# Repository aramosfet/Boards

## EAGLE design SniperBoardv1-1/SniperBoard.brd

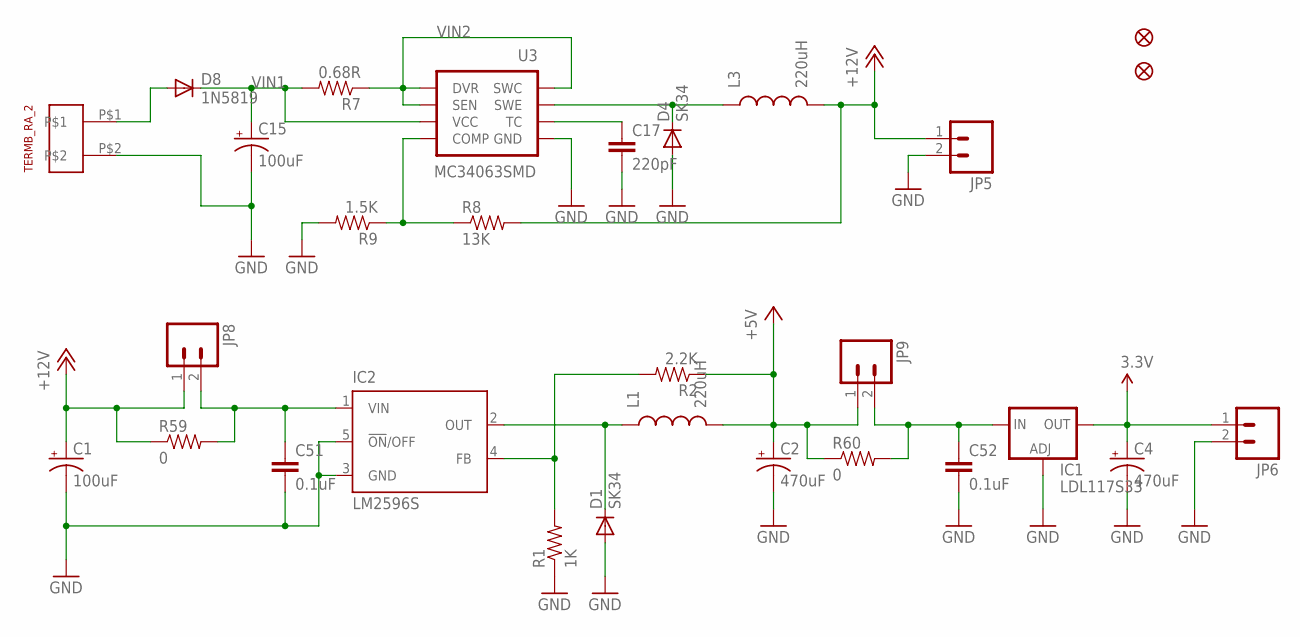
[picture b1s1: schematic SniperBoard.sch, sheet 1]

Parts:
C1, C15: 100uF; PANASONIC_E
C2, C4: 470uF; PANASONIC_E
C17: 220pF; 0805
C51, C52: 0.1uF; 0805
D1, D4: SK34; SMA-DIODE
D8: 1N5819; SMB-DIODE
FID1, FID2: FIDUCIAL1.5X3; FIDUCIAL-1.5X3
IC1: LDL117S33; DPACK
IC2: LM2596S; TO263-5
JP5, JP6: M02POLAR; MOLEX-1X2
JP8, JP9: M02PTH; 1X02
L1, L3: 220uH; RLB914-IND
R1: 1K; 0805
R2: 2.2K; 0805
R7: 0.68R; 0805
R8: 13K; 0805
R9: 1.5K; 0805
R59, R60: 0; 0805
U3: MC34063SMD; SO08
U$2: 1X02_TERMB_RA

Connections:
3.3V: C4.+, IC1.4 (OUT), JP6.1; also elsewhere on the board
+5V: C2.+, JP9.1, L1.P$2 (2), R2.1, R60.1
+12V: C1.+, JP5.1, JP8.1, L3.P$2 (2), R8.2, R59.1; also elsewhere on the board
GND: C1.-, C2.-, C4.-, C15.-, C17.2, C51.2, C52.2, D1.A, D4.A, IC1.1 (ADJ), IC2.3 (GND), IC2.5 (!ON!/OFF), JP5.2, JP6.2, R1.1, R9.2, U3.4 (GND), U$2.P$2; also elsewhere on the board
unnamed: IC2.4 (FB), R1.2, R2.2
unnamed: D1.C, IC2.2 (OUT), L1.P$1 (1)
unnamed: C17.1, U3.3 (TC)
unnamed: D4.C, L3.P$1 (1), U3.2 (SWE)
unnamed: R8.1, R9.1, U3.5 (COMP)
unnamed: D8.A, U$2.P$1
unnamed: C52.1, IC1.3 (IN), JP9.2, R60.2
unnamed: C51.1, IC2.1 (VIN), JP8.2, R59.2
VIN1: C15.+, D8.C, R7.2, U3.6 (VCC)
VIN2: R7.1, U3.1 (SWC), U3.7 (SEN), U3.8 (DVR)

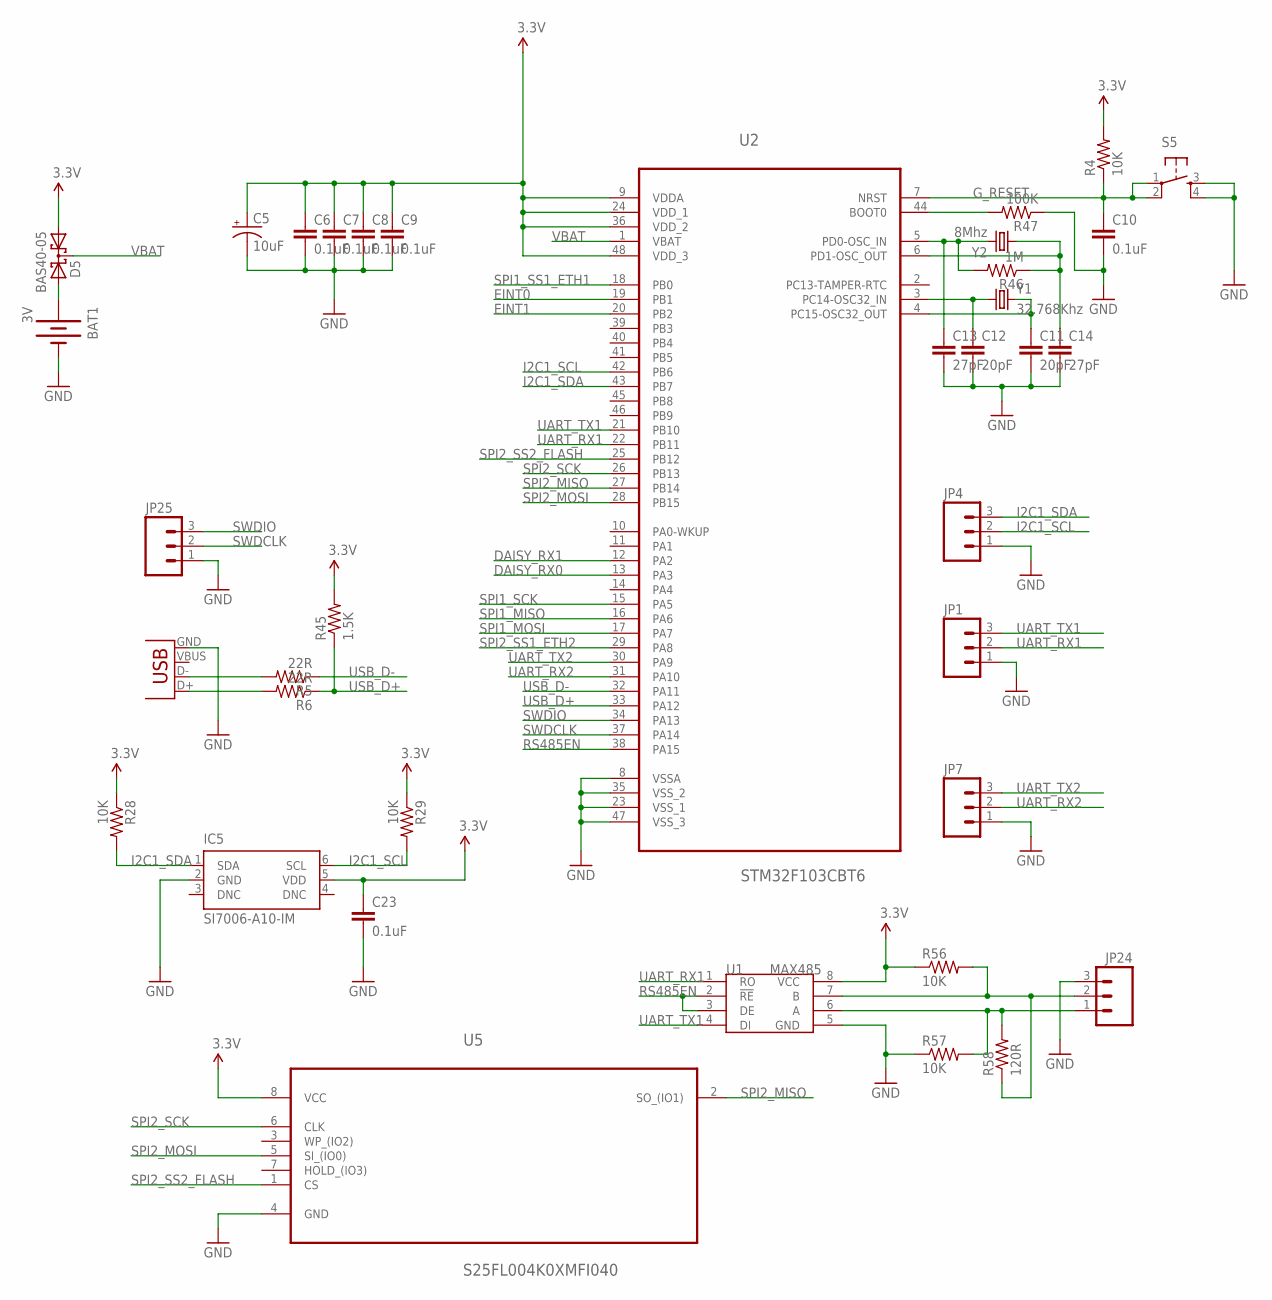
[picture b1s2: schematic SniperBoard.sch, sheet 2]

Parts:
BAT1: 3V; BATTCOM_20MM_PTH
C5: 10uF; EIA3216
C6, C7, C8, C9, C10, C23: 0.1uF; 0805
C11, C12: 20pF; 0805
C13, C14: 27pF; 0805
D5: BAS40-05; SOT23
IC5: SI7006-A10-IM; DFN6-3X3
JP1, JP4, JP7: M03PTH; 1X03
JP3: USB-B; USB-B-PTH
JP24: M03-SCREW-5MM; SCREWTERMINAL-5MM-3
JP25: M03POLAR; MOLEX-1X3
R4, R28, R29, R56, R57: 10K; 0805
R5, R6: 22R; 0805
R45: 1.5K; 0805
R46: 1M; 0805
R47: 100K; 0805
R58: 120R; 1206
S5: TAC_SWITCHPTH; TACTILE-PTH
U1: MAX485; SOP8
U2: STM32F103CBT6; QFP50P900X900X160-48N
U5: S25FL004K0XMFI040; SOIC127P600X175-8N
Y1: 32.768Khz; MC-306
Y2: 8Mhz; HC49US

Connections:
3.3V: C5.A (+), C6.1, C7.1, C8.1, C9.1, C23.1, D5.1 (A1), IC5.5 (VDD), R4.2, R28.1, R29.1, R45.2, R56.1, U1.8 (VCC), U2.9 (VDDA), U2.24 (VDD_1), U2.36 (VDD_2), U2.48 (VDD_3), U5.8 (VCC); also elsewhere on the board
BOOT0: R47.2, U2.44 (BOOT0)
DAISY_RX0: U2.13 (PA3); also elsewhere on the board
DAISY_RX1: U2.12 (PA2); also elsewhere on the board
EINT0: U2.19 (PB1); also elsewhere on the board
EINT1: U2.20 (PB2); also elsewhere on the board
GND: BAT1.2 (-), C5.C (-), C6.2, C7.2, C8.2, C9.2, C10.2, C11.2, C12.2, C13.2, C14.2, C23.2, IC5.2 (GND), JP1.1, JP3.GND, JP4.1, JP7.1, JP24.3, JP25.1, R47.1, R57.1, S5.3, S5.4, U1.5 (GND), U2.8 (VSSA), U2.23 (VSS_1), U2.35 (VSS_2), U2.47 (VSS_3), U5.4 (GND); also elsewhere on the board
G_RESET: C10.1, R4.1, S5.1, S5.2, U2.7 (NRST); also elsewhere on the board
I2C1_SCL: IC5.6 (SCL), JP4.2, R29.2, U2.42 (PB6)
I2C1_SDA: IC5.1 (SDA), JP4.3, R28.2, U2.43 (PB7)
unnamed: BAT1.1 (+), D5.2 (A2)
unnamed: JP24.1, R57.2, R58.2, U1.6 (A)
unnamed: C14.1, R46.1, U2.6 (PD1-OSC_OUT), Y2.1
unnamed: JP3.D-, R5.2
unnamed: JP3.D+, R6.2
unnamed: C12.1, U2.3 (PC14-OSC32_IN), Y1.1
unnamed: C11.1, U2.4 (PC15-OSC32_OUT), Y1.4 (2)
unnamed: C13.1, R46.2, U2.5 (PD0-OSC_IN), Y2.2
unnamed: JP24.2, R56.2, R58.1, U1.7 (B)
RS485EN: U1.2 (!RE), U1.3 (DE), U2.38 (PA15)
SPI1_MISO: U2.16 (PA6); also elsewhere on the board
SPI1_MOSI: U2.17 (PA7); also elsewhere on the board
SPI1_SCK: U2.15 (PA5); also elsewhere on the board
SPI1_SS1_ETH1: U2.18 (PB0); also elsewhere on the board
SPI2_MISO: U2.27 (PB14), U5.2 (SO_(IO1)); also elsewhere on the board
SPI2_MOSI: U2.28 (PB15), U5.5 (SI_(IO0)); also elsewhere on the board
SPI2_SCK: U2.26 (PB13), U5.6 (CLK); also elsewhere on the board
SPI2_SS1_ETH2: U2.29 (PA8); also elsewhere on the board
SPI2_SS2_FLASH: U2.25 (PB12), U5.1 (CS)
SWDCLK: JP25.2, U2.37 (PA14)
SWDIO: JP25.3, U2.34 (PA13)
UART_RX1: JP1.2, U1.1 (RO), U2.22 (PB11)
UART_RX2: JP7.2, U2.31 (PA10); also elsewhere on the board
UART_TX1: JP1.3, U1.4 (DI), U2.21 (PB10)
UART_TX2: JP7.3, U2.30 (PA9); also elsewhere on the board
USB_D+: R6.1, R45.1, U2.33 (PA12)
USB_D-: R5.1, U2.32 (PA11)
VBAT: D5.3 (C), U2.1 (VBAT)

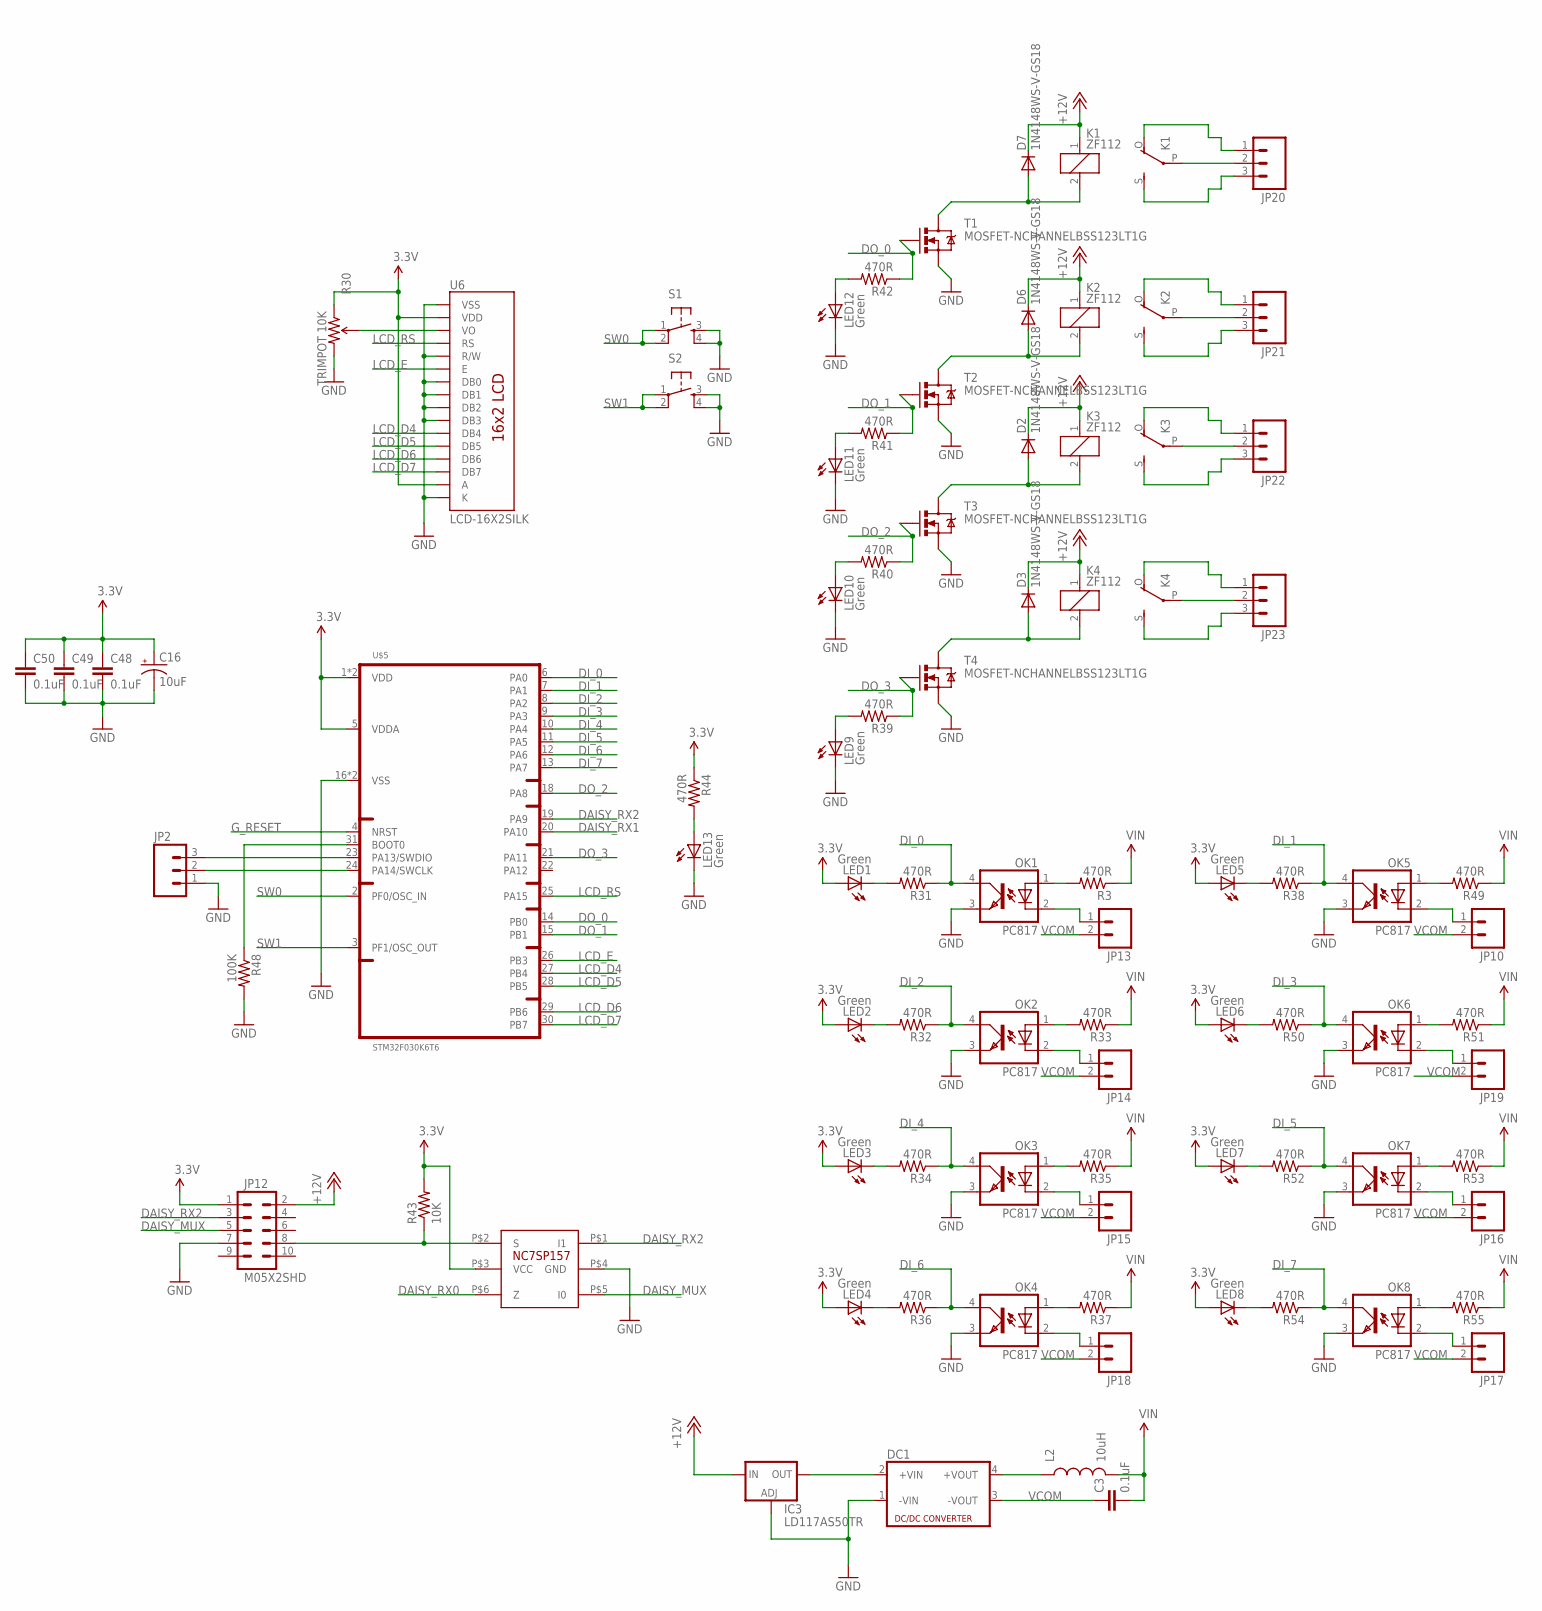
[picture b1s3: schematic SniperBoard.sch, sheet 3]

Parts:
C3, C48, C49, C50: 0.1uF; 0805
C16: 10uF; EIA3216
D2, D3, D6, D7: 1N4148WS-V-GS18; SMA-DIODE_ALT
DC1: NME
IC3: LD117AS50TR; SOT223
JP2: M03POLAR; MOLEX-1X3
JP10, JP13, JP14, JP15, JP16, JP17, JP18, JP19: M025MM; SCREWTERMINAL-5MM-2
JP12: M05X2SHD; 2X5-SHROUDED
JP20, JP21, JP22, JP23: M03-SCREW-5MM; SCREWTERMINAL-5MM-3
K1, K2, K3, K4: ZF112
L2: 10uH; 0805
LED1, LED2, LED3, LED4, LED5, LED6, LED7, LED8, LED9, LED10, LED11, LED12, LED13: Green; LED-1206
OK1, OK2, OK3, OK4, OK5, OK6, OK7, OK8: PC817; DIL04
R3, R31, R32, R33, R34, R35, R36, R37, R38, R39, R40, R41, R42, R44, R49, R50, R51, R52, R53, R54, R55: 470R; 0805
R30: TRIMPOT 10K; TRIM_POT_PTH
R43: 10K; 0805
R48: 100K; 0805
S1, S2: TAC_SWITCHPTH; TACTILE-PTH
T1, T2, T3, T4: MOSFET-NCHANNELBSS123LT1G; SOT23
U6: LCD-16X2SILK; LCD-16X2
U$4: NC7SP157; SC70-6
U$5: STM32F030K6T6; LQFP32-7X7

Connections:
3.3V: C16.A (+), C48.1, C49.1, C50.1, JP12.1, LED1.A, LED2.A, LED3.A, LED4.A, LED5.A, LED6.A, LED7.A, LED8.A, R30.1 (CCW), R43.2, R44.1, U6.2 (VDD), U6.15 (A), U$4.P$3 (VCC), U$5.1 (VDD), U$5.5 (VDDA), U$5.17 (VDD); also elsewhere on the board
+12V: D2.C, D3.C, D6.C, D7.C, IC3.3 (IN), JP12.2, K1.1, K2.1, K3.1, K4.1; also elsewhere on the board
DAISY_MUX: JP12.5, U$4.P$5 (I0)
DAISY_RX0: U$4.P$6 (Z); also elsewhere on the board
DAISY_RX1: U$5.20 (PA10); also elsewhere on the board
DAISY_RX2: JP12.3, U$4.P$1 (I1), U$5.19 (PA9)
DI_0: OK1.4 (COL), R31.1, U$5.6 (PA0)
DI_1: OK5.4 (COL), R38.1, U$5.7 (PA1)
DI_2: OK2.4 (COL), R32.1, U$5.8 (PA2)
DI_3: OK6.4 (COL), R50.1, U$5.9 (PA3)
DI_4: OK3.4 (COL), R34.1, U$5.10 (PA4)
DI_5: OK7.4 (COL), R52.1, U$5.11 (PA5)
DI_6: OK4.4 (COL), R36.1, U$5.12 (PA6)
DI_7: OK8.4 (COL), R54.1, U$5.13 (PA7)
DO_0: R42.1, T1.1 (G), U$5.14 (PB0)
DO_1: R41.1, T2.1 (G), U$5.15 (PB1)
DO_2: R40.1, T3.1 (G), U$5.18 (PA8)
DO_3: R39.1, T4.1 (G), U$5.21 (PA11)
GND: C16.C (-), C48.2, C49.2, C50.2, DC1.1 (-VIN), IC3.1 (ADJ), JP2.1, JP12.7, LED9.C, LED10.C, LED11.C, LED12.C, LED13.C, OK1.3 (EMIT), OK2.3 (EMIT), OK3.3 (EMIT), OK4.3 (EMIT), OK5.3 (EMIT), OK6.3 (EMIT), OK7.3 (EMIT), OK8.3 (EMIT), R30.3 (CW), R48.2, S1.3, S1.4, S2.3, S2.4, T1.2 (S), T2.2 (S), T3.2 (S), T4.2 (S), U6.1 (VSS), U6.5 (R/W), U6.7 (DB0), U6.8 (DB1), U6.9 (DB2), U6.10 (DB3), U6.16 (K), U$4.P$4 (GND), U$5.16 (VSS), U$5.32 (VSS); also elsewhere on the board
G_RESET: U$5.4 (NRST); also elsewhere on the board
LCD_D4: U6.11 (DB4), U$5.27 (PB4)
LCD_D5: U6.12 (DB5), U$5.28 (PB5)
LCD_D6: U6.13 (DB6), U$5.29 (PB6)
LCD_D7: U6.14 (DB7), U$5.30 (PB7)
LCD_E: U6.6 (E), U$5.26 (PB3)
LCD_RS: U6.4 (RS), U$5.25 (PA15)
unnamed: JP20.2, K1.P
unnamed: LED1.C, R31.2
unnamed: LED13.A, R44.2
unnamed: OK2.1 (A), R33.2
unnamed: R30.2 (WIPER), U6.3 (VO)
unnamed: JP23.1, K4.O
unnamed: R48.1, U$5.31 (BOOT0)
unnamed: OK1.1 (A), R3.2
unnamed: JP13.1, OK1.2 (C)
unnamed: JP14.1, OK2.2 (C)
unnamed: JP23.3, K4.S
unnamed: LED2.C, R32.2
unnamed: DC1.4 (+VOUT), L2.1
unnamed: DC1.2 (+VIN), IC3.4 (OUT)
unnamed: JP22.3, K3.S
unnamed: JP21.2, K2.P
unnamed: JP22.1, K3.O
unnamed: JP21.1, K2.O
unnamed: JP21.3, K2.S
unnamed: JP22.2, K3.P
unnamed: JP20.1, K1.O
unnamed: JP23.2, K4.P
unnamed: JP20.3, K1.S
unnamed: D7.A, K1.2, T1.3 (D)
unnamed: D6.A, K2.2, T2.3 (D)
unnamed: D2.A, K3.2, T3.3 (D)
unnamed: D3.A, K4.2, T4.3 (D)
unnamed: LED12.A, R42.2
unnamed: LED11.A, R41.2
unnamed: JP2.3, U$5.23 (PA13/SWDIO)
unnamed: LED10.A, R40.2
unnamed: JP2.2, U$5.24 (PA14/SWCLK)
unnamed: LED9.A, R39.2
unnamed: OK3.1 (A), R35.2
unnamed: JP15.1, OK3.2 (C)
unnamed: LED3.C, R34.2
unnamed: JP12.8, R43.1, U$4.P$2 (S)
unnamed: OK4.1 (A), R37.2
unnamed: JP18.1, OK4.2 (C)
unnamed: LED4.C, R36.2
unnamed: OK5.1 (A), R49.2
unnamed: JP10.1, OK5.2 (C)
unnamed: LED5.C, R38.2
unnamed: OK6.1 (A), R51.2
unnamed: JP19.1, OK6.2 (C)
unnamed: LED6.C, R50.2
unnamed: OK7.1 (A), R53.2
unnamed: JP16.1, OK7.2 (C)
unnamed: LED7.C, R52.2
unnamed: OK8.1 (A), R55.2
unnamed: JP17.1, OK8.2 (C)
unnamed: LED8.C, R54.2
SW0: S1.1, S1.2, U$5.2 (PF0/OSC_IN)
SW1: S2.1, S2.2, U$5.3 (PF1/OSC_OUT)
VCOM: C3.1, DC1.3 (-VOUT), JP10.2, JP13.2, JP14.2, JP15.2, JP16.2, JP17.2, JP18.2, JP19.2
VIN: C3.2, L2.2, R3.1, R33.1, R35.1, R37.1, R49.1, R51.1, R53.1, R55.1

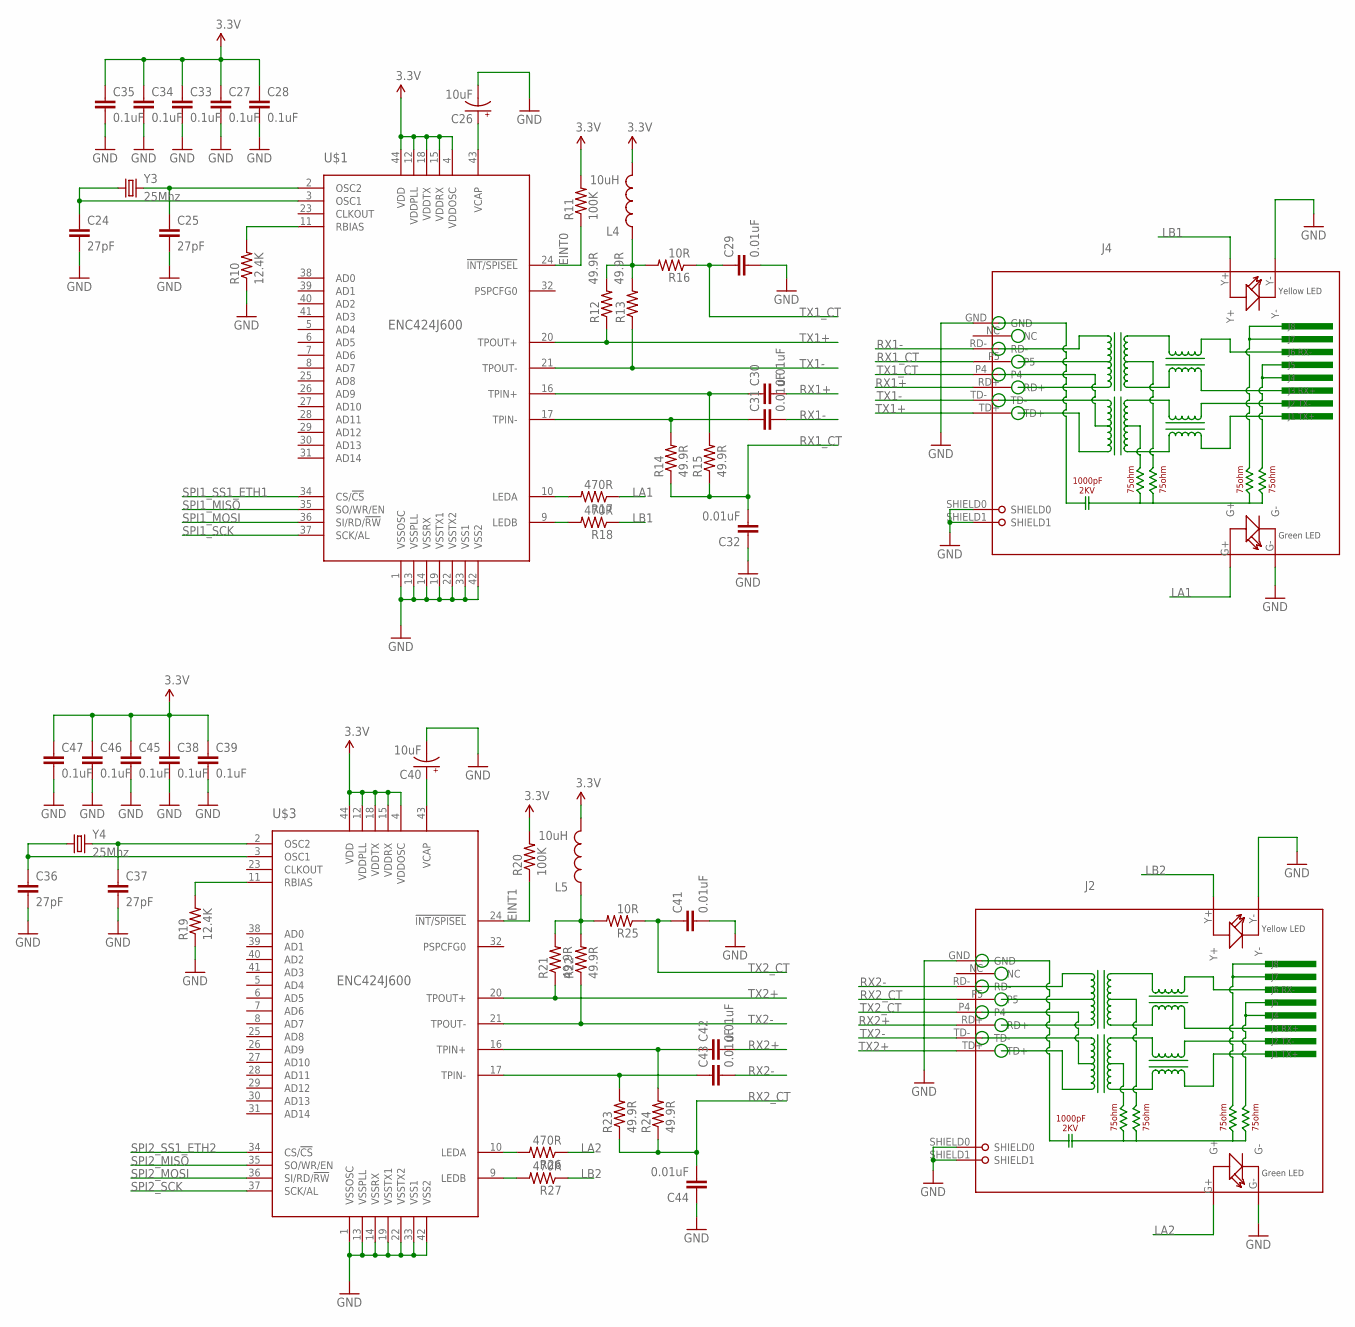
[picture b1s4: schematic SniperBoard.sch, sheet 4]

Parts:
C24, C25, C36, C37: 27pF; 0805
C26, C40: 10uF; EIA3528-KIT
C27, C28, C33, C34, C35, C38, C39, C45, C46, C47: 0.1uF; 0805
C29, C30, C31, C32, C41, C42, C43, C44: 0.01uF; 0805
J2, J4: RJ45-HR911105A-HR911105A; RJMG1BD3B8K1ANR
L4, L5: 10uH; 0805
R10, R19: 12.4K; 0805
R11, R20: 100K; 0805
R12, R13, R14, R15, R21, R22, R23, R24: 49.9R; 0805
R16, R25: 10R; 0805
R17, R18, R26, R27: 470R; 0805
U$1, U$3: ENC424J600; TQFP-44
Y3, Y4: 25Mhz; CRYSTAL-SMD-10.5X4.8-2PIN

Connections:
3.3V: C27.1, C28.1, C33.1, C34.1, C35.1, C38.1, C39.1, C45.1, C46.1, C47.1, L4.2, L5.2, R11.2, R20.2, U$1.4 (VDDOSC), U$1.12 (VDDPLL), U$1.15 (VDDRX), U$1.18 (VDDTX), U$1.44 (VDD), U$3.4 (VDDOSC), U$3.12 (VDDPLL), U$3.15 (VDDRX), U$3.18 (VDDTX), U$3.44 (VDD); also elsewhere on the board
EINT0: R11.1, U$1.24 (!INT/SPISEL); also elsewhere on the board
EINT1: R20.1, U$3.24 (!INT/SPISEL); also elsewhere on the board
GND: C24.2, C25.2, C26.C (-), C27.2, C28.2, C29.2, C32.1, C33.2, C34.2, C35.2, C36.2, C37.2, C38.2, C39.2, C40.C (-), C41.2, C44.1, C45.2, C46.2, C47.2, J2.G-, J2.GND, J2.SHIELD0, J2.SHIELD1, J2.Y-, J4.G-, J4.GND, J4.SHIELD0, J4.SHIELD1, J4.Y-, R10.1, R19.1, U$1.1 (VSSOSC), U$1.13 (VSSPLL), U$1.14 (VSSRX), U$1.19 (VSSTX1), U$1.22 (VSSTX2), U$1.33 (VSS1), U$1.42 (VSS2), U$3.1 (VSSOSC), U$3.13 (VSSPLL), U$3.14 (VSSRX), U$3.19 (VSSTX1), U$3.22 (VSSTX2), U$3.33 (VSS1), U$3.42 (VSS2); also elsewhere on the board
LA1: J4.G+, R17.1
LA2: J2.G+, R26.1
LB1: J4.Y+, R18.1
LB2: J2.Y+, R27.1
unnamed: C24.1, U$1.3 (OSC1), Y3.P$1 (1)
unnamed: C40.A (+), U$3.43 (VCAP)
unnamed: C37.1, U$3.2 (OSC2), Y4.P$2 (2)
unnamed: C30.1, R15.2, U$1.16 (TPIN+)
unnamed: C26.A (+), U$1.43 (VCAP)
unnamed: C31.1, R14.2, U$1.17 (TPIN-)
unnamed: R19.2, U$3.11 (RBIAS)
unnamed: C25.1, U$1.2 (OSC2), Y3.P$2 (2)
unnamed: R10.2, U$1.11 (RBIAS)
unnamed: R17.2, U$1.10 (LEDA)
unnamed: R18.2, U$1.9 (LEDB)
unnamed: L4.1, R12.2, R13.2, R16.2
unnamed: C36.1, U$3.3 (OSC1), Y4.P$1 (1)
unnamed: C42.1, R24.2, U$3.16 (TPIN+)
unnamed: C43.1, R23.2, U$3.17 (TPIN-)
unnamed: L5.1, R21.2, R22.2, R25.2
unnamed: R26.2, U$3.10 (LEDA)
unnamed: R27.2, U$3.9 (LEDB)
RX1+: C30.2, J4.RD+
RX1-: C31.2, J4.RD-
RX1_CT: C32.2, J4.P5, R14.1, R15.1
RX2+: C42.2, J2.RD+
RX2-: C43.2, J2.RD-
RX2_CT: C44.2, J2.P5, R23.1, R24.1
SPI1_MISO: U$1.35 (SO/WR/EN); also elsewhere on the board
SPI1_MOSI: U$1.36 (SI/RD/!RW); also elsewhere on the board
SPI1_SCK: U$1.37 (SCK/AL); also elsewhere on the board
SPI1_SS1_ETH1: U$1.34 (CS/!CS); also elsewhere on the board
SPI2_MISO: U$3.35 (SO/WR/EN); also elsewhere on the board
SPI2_MOSI: U$3.36 (SI/RD/!RW); also elsewhere on the board
SPI2_SCK: U$3.37 (SCK/AL); also elsewhere on the board
SPI2_SS1_ETH2: U$3.34 (CS/!CS); also elsewhere on the board
TX1+: J4.TD+, R12.1, U$1.20 (TPOUT+)
TX1-: J4.TD-, R13.1, U$1.21 (TPOUT-)
TX1_CT: C29.1, J4.P4, R16.1
TX2+: J2.TD+, R21.1, U$3.20 (TPOUT+)
TX2-: J2.TD-, R22.1, U$3.21 (TPOUT-)
TX2_CT: C41.1, J2.P4, R25.1

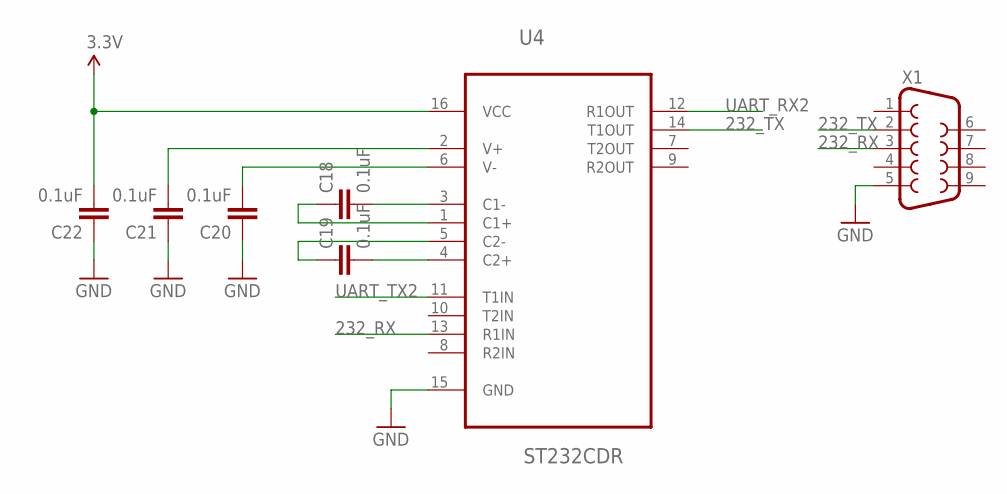
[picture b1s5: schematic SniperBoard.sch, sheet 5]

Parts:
C18, C19, C20, C21, C22: 0.1uF; 0805
U4: ST232CDR; SOIC127P600X175-16N
X1: DB9FEMALE; DB9

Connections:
3.3V: C22.2, U4.16 (VCC); also elsewhere on the board
232_RX: U4.13 (R1IN), X1.3
232_TX: U4.14 (T1OUT), X1.2
GND: C20.1, C21.1, C22.1, U4.15 (GND), X1.5; also elsewhere on the board
unnamed: C21.2, U4.2 (V+)
unnamed: C20.2, U4.6 (V-)
unnamed: C18.2, U4.3 (C1-)
unnamed: C18.1, U4.1 (C1+)
unnamed: C19.1, U4.5 (C2-)
unnamed: C19.2, U4.4 (C2+)
UART_RX2: U4.12 (R1OUT); also elsewhere on the board
UART_TX2: U4.11 (T1IN); also elsewhere on the board

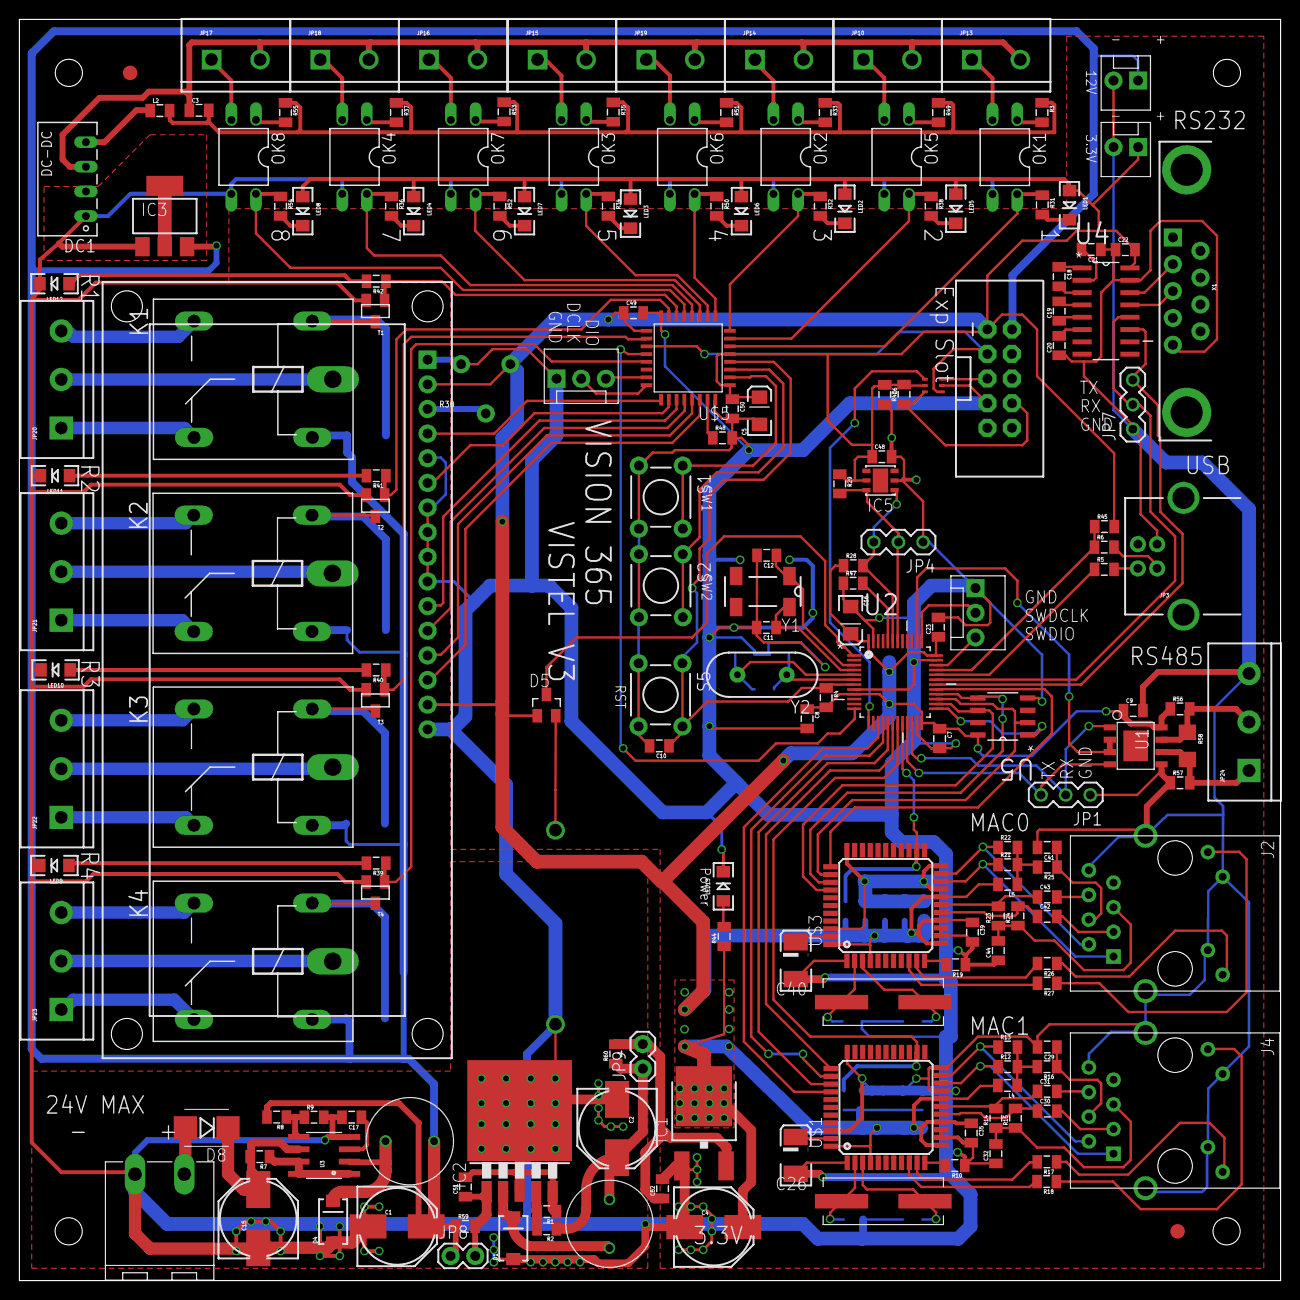
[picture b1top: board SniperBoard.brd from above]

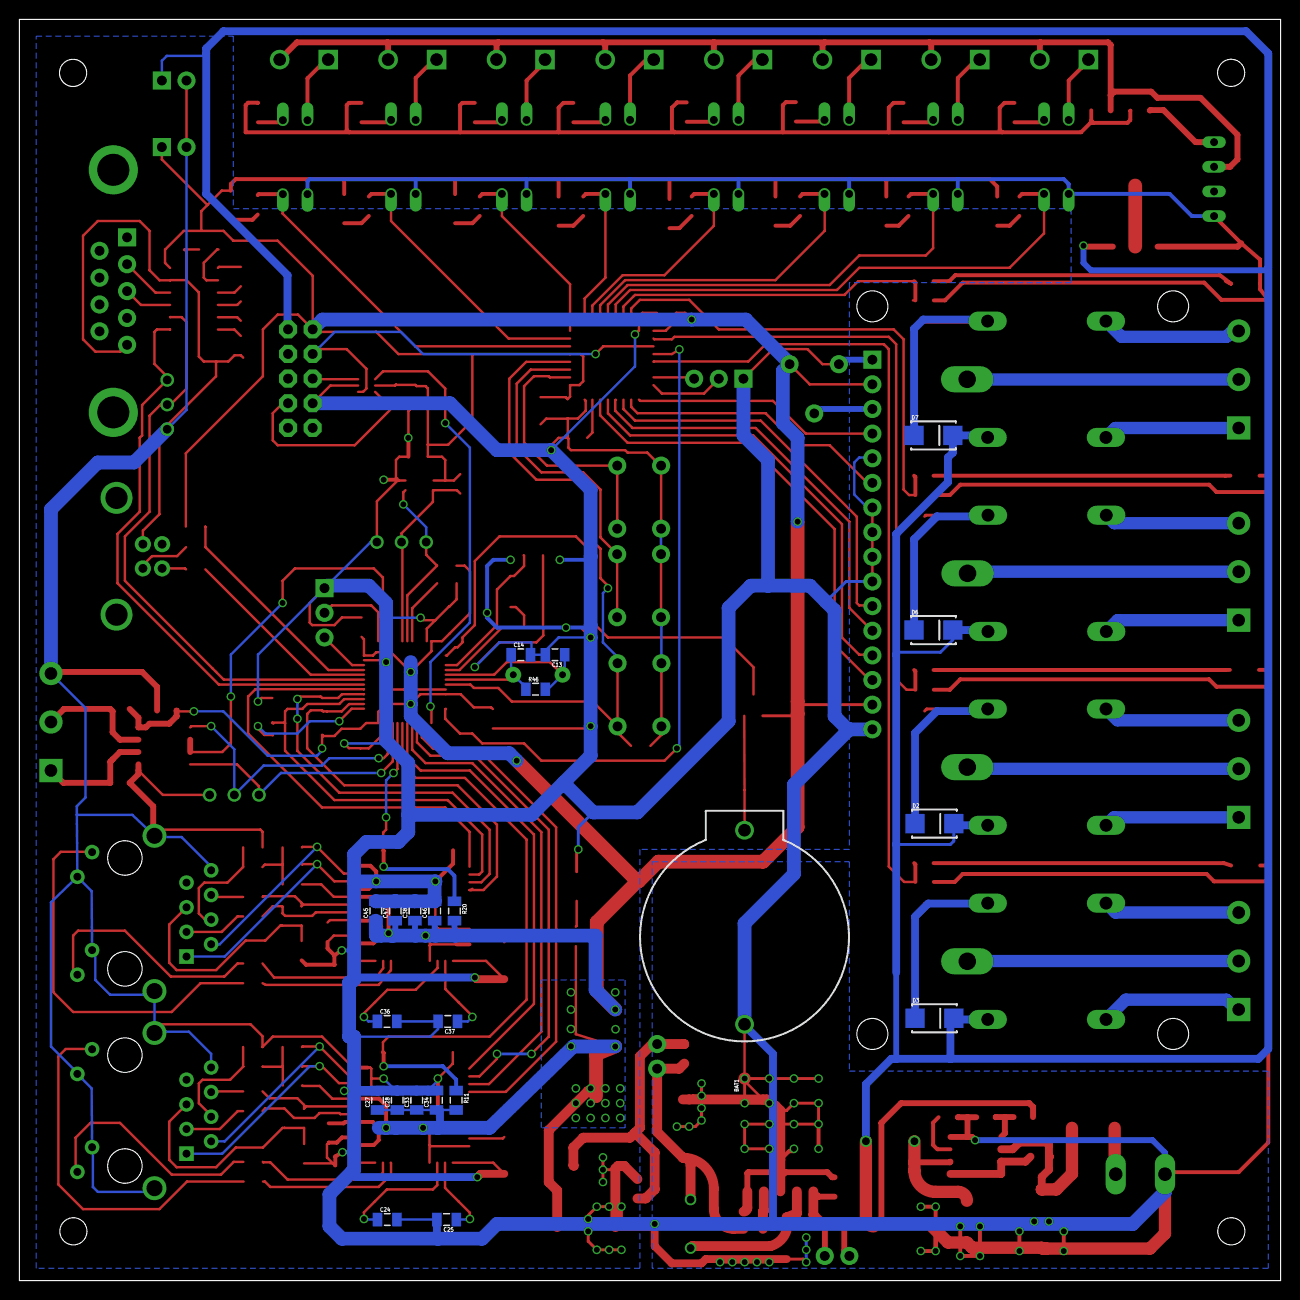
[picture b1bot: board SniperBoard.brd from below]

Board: 2 copper layers, 130.0 x 130.0 mm, 207 parts (22 on the bottom side), 168 nets.

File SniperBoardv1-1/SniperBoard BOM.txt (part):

Partlist exported from D:/Development/Boards/SniperBoardv1-1/SniperBoard.sch at 25/11/2017 12:58:10 PM

Part  Value                     Device                    Package                   Description                                                                         MF                      MPN                            OC_FARNELL OC_NEWARK PACKAGE PROD_ID     SUPPLIER           VALUE
BAT1  3V                        BATTERY20PTH              BATTCOM_20MM_PTH          Battery Holders                                                                                                                                                                                             
C1    100uF                     CAP_POLE                  PANASONIC_E               Capacitor Polarized                                                                                                                                                                                         
C2    470uF                     CAP_POLE                  PANASONIC_E               Capacitor Polarized                                                                                                                                                                                         
C3    0.1uF                     CAP0805                   0805                      Capacitor                                                                                                                                                                                                   
C4    470uF                     CAP_POLE                  PANASONIC_E               Capacitor Polarized                                                                                                                                                                                         
C5    10uF                      10UF-TANT                 EIA3216                   10uF Tantalum SMT                                                                                                                                                       CAP-00811                      10uF 
C6    0.1uF                     CAP0805                   0805                      Capacitor                                                                                                                                                                                                   
C7    0.1uF                     CAP0805                   0805                      Capacitor                                                                                                                                                                                                   
C8    0.1uF                     CAP0805                   0805                      Capacitor                                                                                                                                                                                                   
C9    0.1uF                     CAP0805                   0805                      Capacitor                                                                                                                                                                                                   
C10   0.1uF                     CAP0805                   0805                      Capacitor                                                                                                                                                                                                   
C11   20pF                      CAP0805                   0805                      Capacitor                                                                                                                                                                                                   
C12   20pF                      CAP0805                   0805                      Capacitor                                                                                                                                                                                                   
C13   27pF                      CAP0805                   0805                      Capacitor                                                                                                                                                                                                   
C14   27pF                      CAP0805                   0805                      Capacitor                                                                                                                                                                                                   
C15   100uF                     CAP_POLE                  PANASONIC_E               Capacitor Polarized                                                                                                                                                                                         
C16   10uF                      10UF-TANT                 EIA3216                   10uF Tantalum SMT                                                                                                                                                       CAP-00811                      10uF 
C17   220pF                     CAP0805                   0805                      Capacitor                                                                                                                                                                                                   
C18   0.1uF                     CAP0805                   0805                      Capacitor                                                                                                                                                                                                   
C19   0.1uF                     CAP0805                   0805                      Capacitor                                                                                                                                                                                                   
C20   0.1uF                     CAP0805                   0805                      Capacitor                                                                                                                                                                                                   
C21   0.1uF                     CAP0805                   0805                      Capacitor                                                                                                                                                                                                   
C22   0.1uF                     CAP0805                   0805                      Capacitor                                                                                                                                                                                                   
C23   0.1uF                     CAP0805                   0805                      Capacitor                                                                                                                                                                                                   
C24   27pF                      CAP0805                   0805                      Capacitor                                                                                                                                                                                                   
C25   27pF                      CAP0805                   0805                      Capacitor                                                                                                                                                                                                   
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
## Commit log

2017-11-15 Vistel Board
    Initial Commit
2017-11-16 Test Commit
    Second Commit Test
2017-11-16 Update2
2017-11-19 Updated Power suply section
2017-11-26 SniperBoard v1.1 Updated

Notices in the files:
parts and their libraries:
SparkFun-PowerIC: Licensing: CC v3.0 Share-Alike You are welcome to use this library for commercial purposes.
si70xx-10: (c) 2014 Samuel Lourenço
